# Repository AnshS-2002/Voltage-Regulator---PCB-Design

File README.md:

# Voltage-Regulator---PCB-Design
Welcome to the Voltage Regulator PCB Design repository! Here, we explore efficient and reliable ways to regulate voltage for various electronic applications. Whether you’re building a power supply, an embedded system, or a hobby project, this repository has you covered. Please be free to solve any errors on EDC or DRC.
Download the raw files to open the schemtic and pcb layout.

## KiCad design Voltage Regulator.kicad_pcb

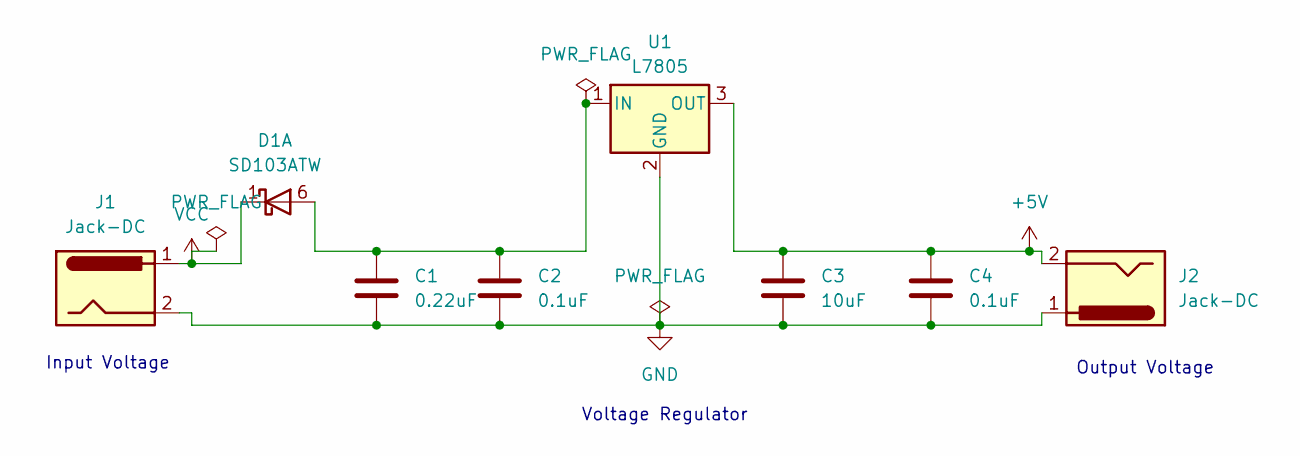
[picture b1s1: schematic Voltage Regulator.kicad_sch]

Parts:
C1: 0.22uF; C_0201_0603Metric_Pad0.64x0.40mm_HandSolder
C2, C4: 0.1uF; C_0201_0603Metric_Pad0.64x0.40mm_HandSolder
C3: 10uF; C_0201_0603Metric_Pad0.64x0.40mm_HandSolder
D1: SD103ATW; SOT-363_SC-70-6
J1, J2: Jack-DC; BarrelJack_SwitchcraftConxall_RAPC10U_Horizontal
U1: L7805; TO-220-3_Vertical

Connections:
+5V: C3.1, C4.1, J2.2, U1.3 (OUT)
GND: C1.2, C2.2, C3.2, C4.2, J1.2, J2.1, U1.2 (GND)
unnamed: C1.1, C2.1, D1.6 (A), U1.1 (IN)
VCC: D1.1 (K), J1.1

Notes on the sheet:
Voltage Regulator
Input Voltage
Output Voltage

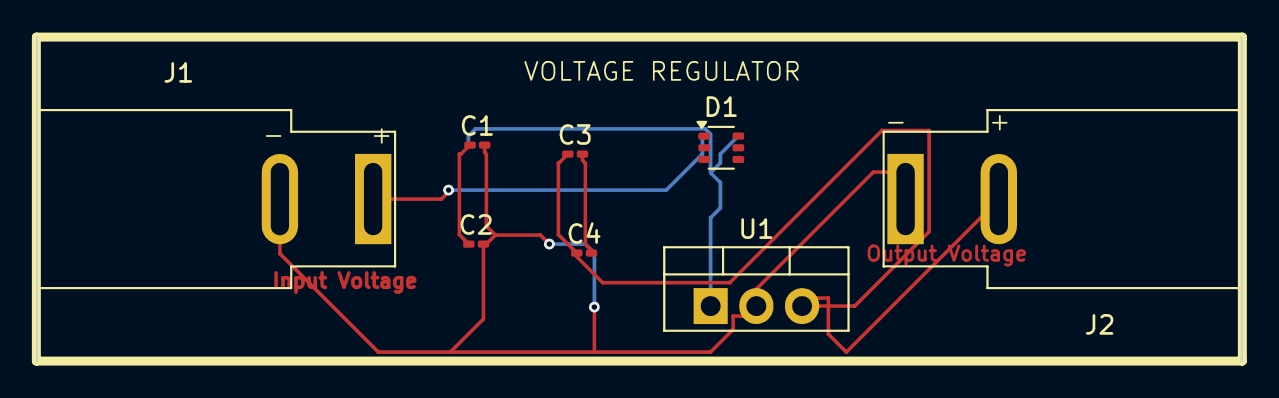
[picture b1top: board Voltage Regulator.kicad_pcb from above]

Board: 2 copper layers, 66.9 x 18.0 mm, 8 parts (0 on the bottom side), 4 nets.
